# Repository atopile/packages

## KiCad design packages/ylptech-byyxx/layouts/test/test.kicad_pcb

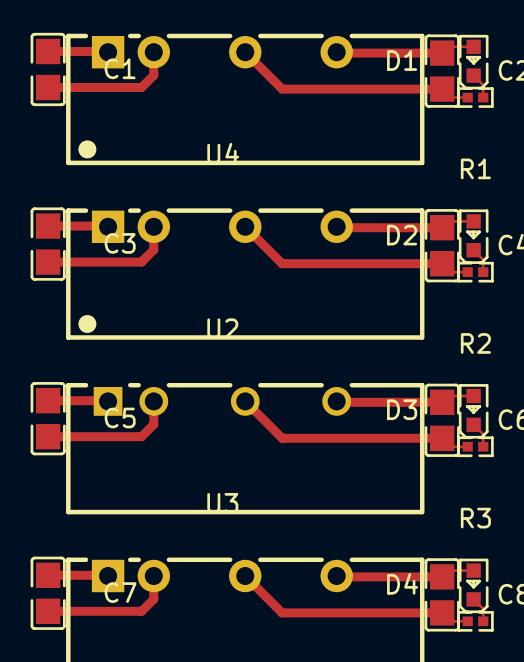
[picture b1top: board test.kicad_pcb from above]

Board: 2 copper layers, 20 parts (0 on the bottom side), 20 nets.

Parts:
C1, C3, C5, C7: 2.2µF ±10% 25V X7R; C0805
C2, C4, C6, C8: 10µF ±10% 25V X5R; C0805
D1, D2, D3, D4: LED0603-RD
R1, R2, R3, R4: 2kΩ ±1% 62.5mW; R0402
U1, U3, U4: PWRM-TH_BXXXXS-2WR3
U2: PWRM-TH_BXXXXS-2WR2

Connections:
current_limiting_resistor-cathode-0: D1.1, R1.1
current_limiting_resistor-cathode-1: D2.1, R2.1
current_limiting_resistor-cathode-2: D3.1, R3.1
current_limiting_resistor-cathode-3: D4.1, R4.1
regulators[0]-power_in-GND: C1.2, U1.2
regulators[0]-power_in-VCC: C1.1, U1.1
regulators[0]-power_out-GND: C2.2, R1.2, U1.4
regulators[0]-power_out-VCC: C2.1, D1.2, U1.6
regulators[1]-power_in-GND: C3.2, U4.2
regulators[1]-power_in-VCC: C3.1, U4.1
regulators[1]-power_out-GND: C4.2, R2.2, U4.4
regulators[1]-power_out-VCC: C4.1, D2.2, U4.6
regulators[2]-power_in-GND: C5.2, U2.2
regulators[2]-power_in-VCC: C5.1, U2.1
regulators[2]-power_out-GND: C6.2, R3.2, U2.4
regulators[2]-power_out-VCC: C6.1, D3.2, U2.6
regulators[3]-power_in-GND: C7.2, U3.2
regulators[3]-power_in-VCC: C7.1, U3.1
regulators[3]-power_out-GND: C8.2, R4.2, U3.4
regulators[3]-power_out-VCC: C8.1, D4.2, U3.6

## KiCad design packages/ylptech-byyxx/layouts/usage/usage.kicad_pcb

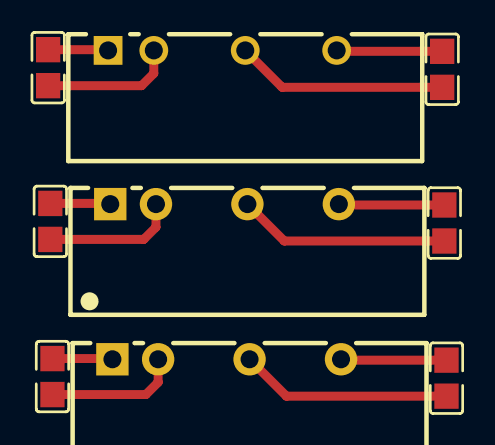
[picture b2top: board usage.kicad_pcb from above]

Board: 2 copper layers, 9 parts (0 on the bottom side), 12 nets.

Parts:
C1, C2, C3, C4, C5, C6: [capacitance: unknown]; C0805
U1, U3: PWRM-TH_BXXXXS-2WR3
U2: PWRM-TH_BXXXXS-2WR2

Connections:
hv: C3.1, U2.1
lv: C3.2, U2.2
reg_5v_to_5v-power_in-hv: C1.1, U1.1
reg_5v_to_5v-power_in-lv: C1.2, U1.2
reg_5v_to_5v-power_out-hv: C2.1, U1.6
reg_5v_to_5v-power_out-lv: C2.2, U1.4
reg_12v_to_5v-power_out-hv: C4.1, U2.6
reg_12v_to_5v-power_out-lv: C4.2, U2.4
reg_24v_to_5v-power_in-hv: C5.1, U3.1
reg_24v_to_5v-power_in-lv: C5.2, U3.2
reg_24v_to_5v-power_out-hv: C6.1, U3.6
reg_24v_to_5v-power_out-lv: C6.2, U3.4

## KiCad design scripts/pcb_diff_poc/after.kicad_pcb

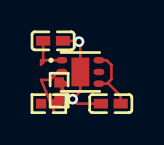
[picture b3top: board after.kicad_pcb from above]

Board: 2 copper layers, 5 parts (0 on the bottom side), 4 nets.

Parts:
C1, C2: 1µF ±10% 25V X5R; C0402
R1, R2: 10kΩ ±1% 62.5mW; R0402
U1: WSON-6_L2.0-W2.0-P0.65-TL-EP

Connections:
GND: C1.2, C2.2, R1.2, U1.3, U1.7
VDIV_OUTPUT: R1.1, R2.2, U1.2
power-VCC: C2.1, R2.1, U1.1
power_in-VCC: C1.1, U1.4, U1.6
